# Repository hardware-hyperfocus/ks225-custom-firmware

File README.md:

# ks225-custom-firmware
An effort to build a custom firmware for Kasa and Tapo light dimmers (e.g. KS225)

## Backups
Flashing backups with either `ltchiptool` *or* `AmebaZII_PGTool` results in errors. So does downloading a full flash image built with `libretiny`, so flashing part by part might work better - TBD.

## Flashing
The firmware can be built for `wbr3` (which I believe was able to flash over the default firmware).

To use `generic-rtl8720cf-2mb-992k`, the separate partitions (partition table, bootloader and only then system) have to be flashed one by one with `AmebaZII_PGTool`.

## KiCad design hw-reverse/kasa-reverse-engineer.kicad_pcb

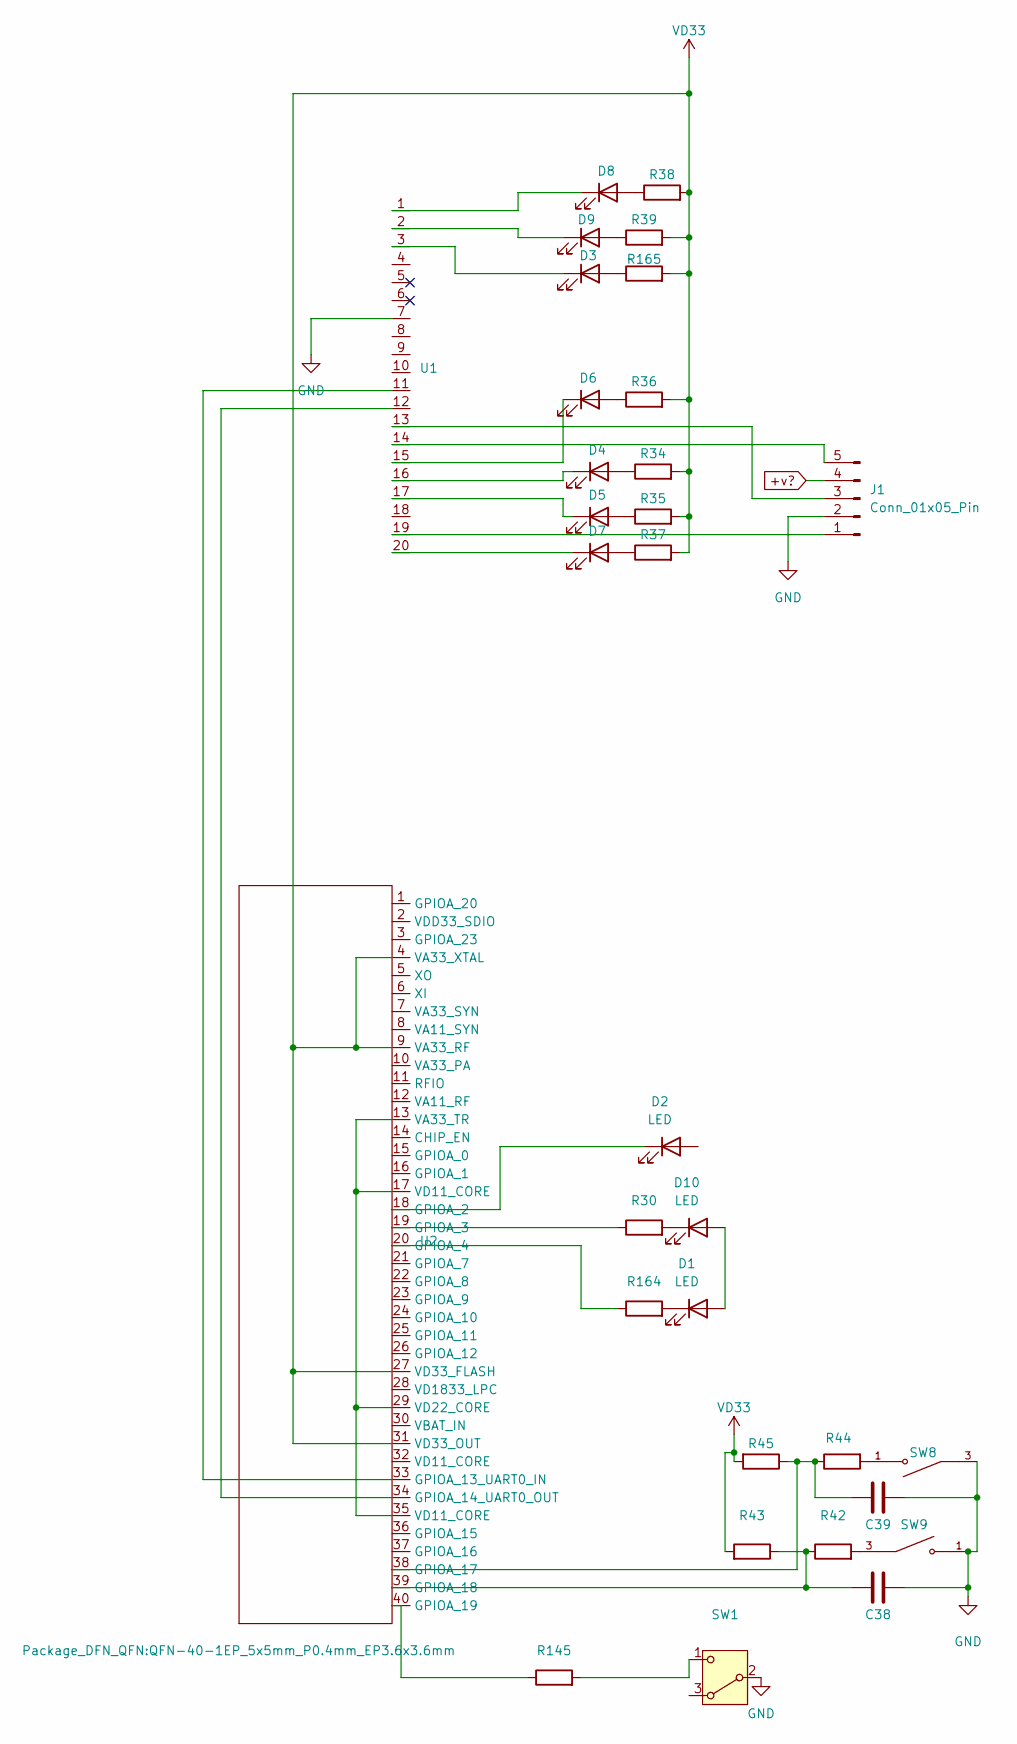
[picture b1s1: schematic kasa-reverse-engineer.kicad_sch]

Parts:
C38, C39: C; C_01005_0402Metric
D1, D2, D3, D4, D5, D6, D7, D8, D9, D10: LED; LED_0201_0603Metric
J1: Conn_01x05_Pin; SIP-5
R30, R42, R43, R44, R45, R145, R164: R; R_01005_0402Metric
R34, R35, R36, R37, R38, R39, R165: R; R_0201_0603Metric
SW1: SW_Wuerth_450301014042; SIP-3
SW8, SW9: PTS_647_SM38_SMTR2_LFS; SW_PTS_647_SM38_SMTR2_LFS; PARTREV 11 Jun 19
U1: TSSOP-20-1EP_4.4x6.5mm_P0.65mm_EP2.15x3.35mm
U2: QFN-40-1EP_5x5mm_P0.4mm_EP3.6x3.6mm

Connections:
+v?: J1.4
GND: C38.2, C39.2, J1.2, SW1.2 (B), SW8.3, SW9.1, U1.7
unnamed: D1.2 (A), D10.2 (A)
unnamed: D1.1 (K), R164.2
unnamed: D2.1 (K), U2.18 (GPIOA_2)
unnamed: D3.2 (A), R165.1
unnamed: D3.1 (K), U1.3
unnamed: D4.2 (A), R34.1
unnamed: D4.1 (K), U1.16
unnamed: D5.2 (A), R35.1
unnamed: D5.1 (K), U1.17
unnamed: D6.2 (A), R36.1
unnamed: D6.1 (K), U1.15
unnamed: D7.2 (A), R37.1
unnamed: D7.1 (K), U1.20
unnamed: D8.2 (A), R38.1
unnamed: D8.1 (K), U1.1
unnamed: D9.2 (A), R39.1
unnamed: D9.1 (K), U1.2
unnamed: D10.1 (K), R30.2
unnamed: J1.1, U1.19
unnamed: J1.3, U1.13
unnamed: J1.5, U1.14
unnamed: R42.2, SW9.3
unnamed: R44.2, SW8.1
unnamed: R145.2, SW1.1
unnamed: R30.1, U2.19 (GPIOA_3)
unnamed: R164.1, U2.20 (GPIOA_4)
unnamed: U1.11, U2.33 (GPIOA_13)
unnamed: U1.12, U2.34 (GPIOA_14)
unnamed: C39.1, R44.1, R45.1, U2.38 (GPIOA_17)
unnamed: C38.1, R42.1, R43.1, U2.39 (GPIOA_18)
unnamed: R145.1, U2.40 (GPIOA_19)
unnamed: U2.13 (VA33_TR), U2.17 (VD11_CORE), U2.29 (VD22_CORE), U2.35 (VD11_CORE)
VD33: R34.2, R35.2, R36.2, R37.2, R38.2, R39.2, R43.2, R45.2, R165.2, U2.4 (VA33_XTAL), U2.9 (VA33_RF), U2.27 (VD33_FLASH), U2.31 (VD33_OUT)

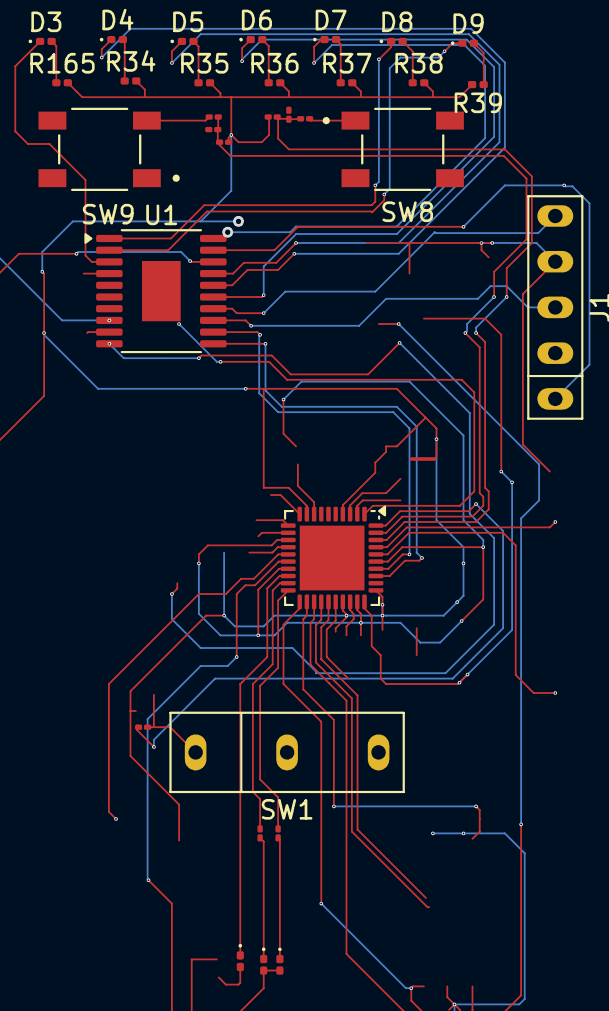
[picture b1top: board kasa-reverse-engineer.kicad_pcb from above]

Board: 2 copper layers, 32 parts (0 on the bottom side), 34 nets.

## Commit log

2024-10-17 Add data I have so far
2024-10-17 Add esphome config
2024-10-17 add flash tools, a bit in readme
